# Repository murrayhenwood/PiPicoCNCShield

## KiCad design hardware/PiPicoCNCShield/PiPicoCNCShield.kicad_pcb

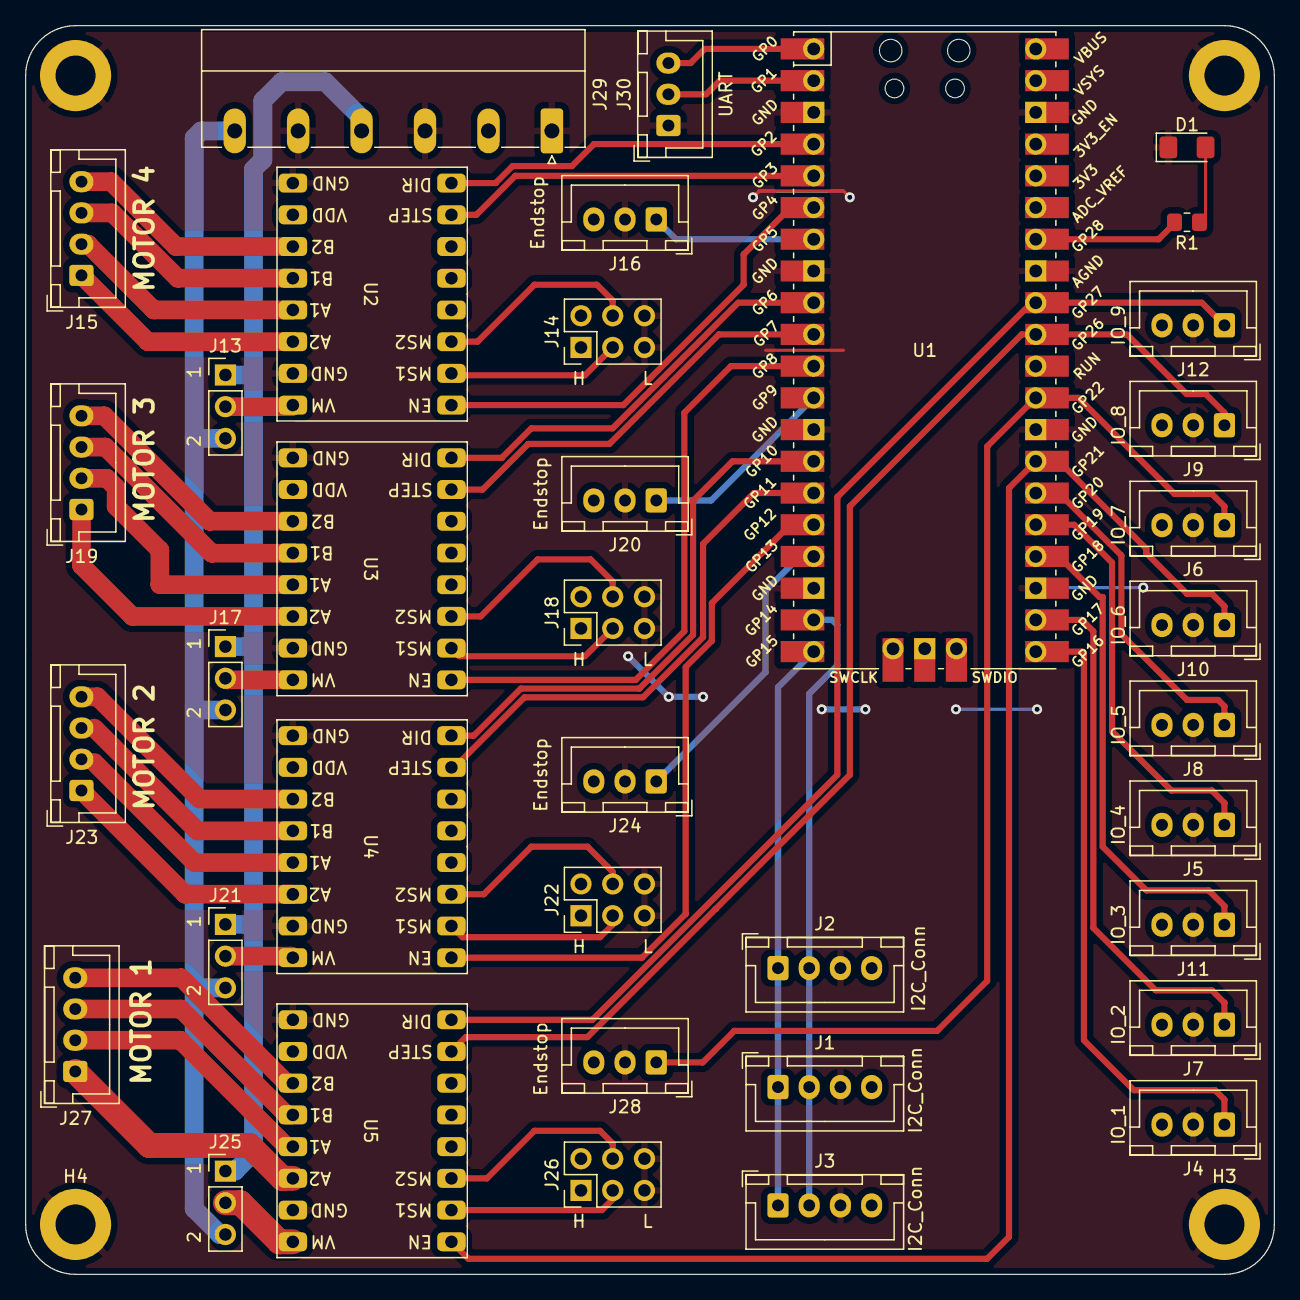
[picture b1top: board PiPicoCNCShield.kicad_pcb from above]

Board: 2 copper layers, 100.0 x 100.0 mm, 41 parts (0 on the bottom side), 59 nets.

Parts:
D1: LED; LED_1206_3216Metric_Pad1.42x1.75mm_HandSolder
H1, H2, H3, H4: MountingHole_Pad; MountingHole_3.2mm_M3_ISO7380_Pad
J1, J2, J3: I2C_Conn; JST_XH_B4B-XH-A_1x04_P2.50mm_Vertical
J4: IO_1; JST_XH_B3B-XH-A_1x03_P2.50mm_Vertical
J5: IO_4; JST_XH_B3B-XH-A_1x03_P2.50mm_Vertical
J6: IO_7; JST_XH_B3B-XH-A_1x03_P2.50mm_Vertical
J7: IO_2; JST_XH_B3B-XH-A_1x03_P2.50mm_Vertical
J8: IO_5; JST_XH_B3B-XH-A_1x03_P2.50mm_Vertical
J9: IO_8; JST_XH_B3B-XH-A_1x03_P2.50mm_Vertical
J10: IO_6; JST_XH_B3B-XH-A_1x03_P2.50mm_Vertical
J11: IO_3; JST_XH_B3B-XH-A_1x03_P2.50mm_Vertical
J12: IO_9; JST_XH_B3B-XH-A_1x03_P2.50mm_Vertical
J13, J17, J21, J25: D_MotorVoltageJumper; PinHeader_1x03_P2.54mm_Vertical
J14, J18, J22, J26: D_MicrostepJumper; PinHeader_2x03_P2.54mm_Vertical
J15, J19, J23, J27: D_MOTOR_Conn; JST_XH_B4B-XH-A_1x04_P2.50mm_Vertical
J16, J20, J24, J28: D_EndStop; JST_XH_B3B-XH-A_1x03_P2.50mm_Vertical
J29: POWER_CONN; PhoenixContact_MC_1,5_6-G-5.08_1x06_P5.08mm_Horizontal
J30: UART; JST_XH_B3B-XH-A_1x03_P2.50mm_Vertical
R1: R; R_0805_2012Metric_Pad1.20x1.40mm_HandSolder
U1: Pico; RPi_Pico_SMD_TH
U2, U3, U4, U5: DriverCarrier

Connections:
3v3: J1.4, J2.4, J3.4, J4.3, J5.3, J6.3, J7.3, J8.3, J9.3, J10.3, J11.3, J12.3, J14.1, J14.2, J16.3, J18.1, J18.2, J20.3, J22.1, J22.2, J24.3, J26.1, J26.2, J28.3, J29.2, U1.36 (3V3), U2.10 (VDD), U3.10 (VDD), U4.10 (VDD), U5.10 (VDD)
D1_DIR: U1.4 (GPIO2), U2.8 (DIR)
D1_EN: U1.6 (GPIO4), U2.1 (EN)
D1_ENDSTOP: J16.1, U1.7 (GPIO5)
D1_STEP: U1.5 (GPIO3), U2.7 (STEP)
D2_DIR: U1.9 (GPIO6), U3.8 (DIR)
D2_EN: U1.11 (GPIO8), U3.1 (EN)
D2_ENDSTOP: J20.1, U1.12 (GPIO9)
D2_STEP: U1.10 (GPIO7), U3.7 (STEP)
D3_DIR: U1.14 (GPIO10), U4.8 (DIR)
D3_EN: U1.16 (GPIO12), U4.1 (EN)
D3_ENDSTOP: J24.1, U1.17 (GPIO13)
D3_STEP: U1.15 (GPIO11), U4.7 (STEP)
GND: D1.1 (K), H1.1, H2.1, H3.1, H4.1, J1.3, J2.3, J3.3, J4.2, J5.2, J6.2, J7.2, J8.2, J9.2, J10.2, J11.2, J12.2, J14.5, J14.6, J16.2, J18.5, J18.6, J20.2, J22.5, J22.6, J24.2, J26.5, J26.6, J28.2, J29.1, J29.3, J29.5, J30.1, U1.3 (GND), U1.8 (GND), U1.13 (GND), U1.18 (GND), U1.23 (GND), U1.28 (GND), U1.33 (AGND), U1.38 (GND), U2.9 (GND), U2.15 (GND), U3.9 (GND), U3.15 (GND), U4.9 (GND), U4.15 (GND), U5.9 (GND), U5.15 (GND)
IO_1_Sig: J4.1, U1.21 (GPIO16)
IO_2_Sig: J7.1, U1.22 (GPIO17)
IO_3_Sig: J11.1, U1.24 (GPIO18)
IO_4_Sig: J5.1, U1.25 (GPIO19)
IO_5_Sig: J8.1, U1.26 (GPIO20)
IO_6_Sig_D4_EN: J10.1, U1.27 (GPIO21), U5.1 (EN)
IO_7_Sig_D4_ENDSTOP: J6.1, J28.1, U1.29 (GPIO22)
IO_8_Sig_D4_STEP: J9.1, U1.31 (GPIO26_ADC0), U5.7 (STEP)
IO_9_Sig_D4_DIR: J12.1, U1.32 (GPIO27_ADC1), U5.8 (DIR)
LED: R1.2, U1.34 (GPIO28_ADC2)
unnamed: D1.2 (A), R1.1
unnamed: J13.2, U2.16 (VM)
unnamed: J14.3, U2.2 (MS1)
unnamed: J14.4, U2.3 (MS2)
unnamed: J15.1, U2.14 (A2)
unnamed: J15.2, U2.13 (A1)
unnamed: J15.3, U2.12 (B1)
unnamed: J15.4, U2.11 (B2)
unnamed: J17.2, U3.16 (VM)
unnamed: J18.3, U3.2 (MS1)
unnamed: J18.4, U3.3 (MS2)
unnamed: J19.1, U3.14 (A2)
unnamed: J19.2, U3.13 (A1)
unnamed: J19.3, U3.12 (B1)
unnamed: J19.4, U3.11 (B2)
unnamed: J21.2, U4.16 (VM)
unnamed: J22.3, U4.2 (MS1)
unnamed: J22.4, U4.3 (MS2)
unnamed: J23.1, U4.14 (A2)
unnamed: J23.2, U4.13 (A1)
unnamed: J23.3, U4.12 (B1)
unnamed: J23.4, U4.11 (B2)
unnamed: J25.2, U5.16 (VM)
unnamed: J26.3, U5.2 (MS1)
unnamed: J26.4, U5.3 (MS2)
unnamed: J27.1, U5.14 (A2)
unnamed: J27.2, U5.13 (A1)
unnamed: J27.3, U5.12 (B1)
unnamed: J27.4, U5.11 (B2)
RX: J30.2, U1.2 (GPIO1)
SCL: J1.1, J2.1, J3.1, U1.20 (GPIO15)
SDA: J1.2, J2.2, J3.2, U1.19 (GPIO14)
TX: J30.3, U1.1 (GPIO0)
VM_1: J13.1, J17.1, J21.1, J25.1, J29.4
VM_2: J13.3, J17.3, J21.3, J25.3, J29.6

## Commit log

2022-10-20 Initial Work
    Draft schematic
2022-10-20 Driver Carrier sub-schematic
    Driver Carrier sub-schematic
2022-10-20 Initial PCB design
    Initial PCB design
2022-10-21 Test run
